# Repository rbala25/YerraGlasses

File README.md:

# YerraGlasses
 
Audio-augmented smart glasses that act as a wearable guide dog — real-time object detection converted to spatial audio feedback, all running on an ESP32-S3 tucked inside a glasses frame.
 
---
 
## Highlights
 
**Embedded ML Object Detection** — Neural network running on a **Luckfox RV1103 NPU** detects objects from live visual input and converts them into real-time auditory cues. Designed to assist blind and visually impaired users without any cloud dependency.
 
**Dual I2S Class-D Audio** — Two Class-D amplifiers driven over I2S deliver low-latency directional audio feedback. Custom DAC and speaker amplification stages built discrete, with 26-gauge wire crimped and routed by hand to fit the form factor.
 
**Space-Constrained PCB** — Custom board designed to fit inside a glasses frame. Integrates USB-C input, rail regulation, I2C sensor communication, and the full I2S audio pipeline — all in a footprint small enough to wear.
 
**Power System** — Robust battery management with USB-C charging, regulated power rails, and firmware-level power state detection to maximize battery life in a miniature form factor.
 
---
 
## Stack
 
| Layer | Tech |
|---|---|
| MCU | ESP32-S3 |
| Language | C, bare-metal |
| ML Inference | Luckfox RV1103 NPU (object detection) |
| Audio | Dual I2S Class-D amps + custom DAC |
| Communication | I2C |
| Power | USB-C + regulated rails + battery monitoring |
| Hardware | Custom PCB, 26-gauge hand-crimped wiring |

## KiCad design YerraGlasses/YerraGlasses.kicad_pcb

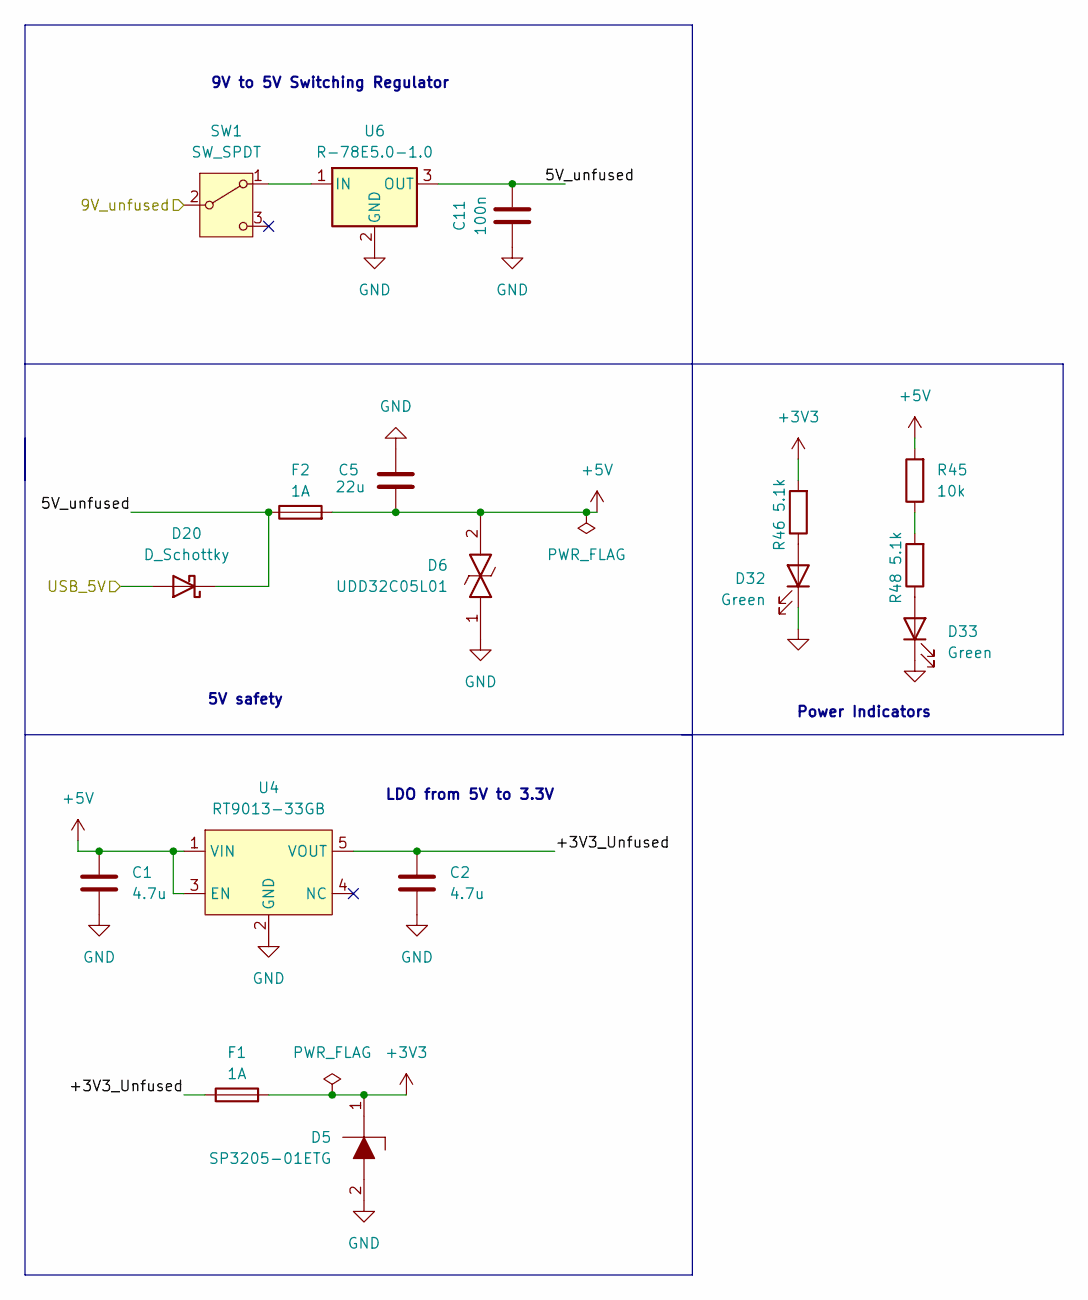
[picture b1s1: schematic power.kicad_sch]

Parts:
C1, C2: 4.7u; C_1206_3216Metric_Pad1.33x1.80mm_HandSolder; Mouser # 187-CL31A475KBHNNNE
C5: 22u; C_0603_1608Metric_Pad1.08x0.95mm_HandSolder; Mouser # 963-A168BB5226MTNA01
C11: 100n; C_0603_1608Metric_Pad1.08x0.95mm_HandSolder; Mouser # 581-KAM15BR72A104KT
D5: SP3205-01ETG; SP320501ETG; Mouser # 576-SP3205-01ETG
D6: UDD32C05L01; D_SOD-323; Mouser # 603-UDD32C05L01
D20: D_Schottky; D_PowerDI-123; Mouser # 621-DFLS160-F
D32, D33: Green; D_0603_1608Metric_Pad1.05x0.95mm_HandSolder; Mouser # 604-APT1608LZGCK
F1, F2: 1A; Fuse_0603_1608Metric_Pad1.05x0.95mm_HandSolder; Mouser # 504-TR-0603HV1-R
R45: 10k; R_0603_1608Metric_Pad0.98x0.95mm_HandSolder; Mouser # 71-CRCW0603-10K-E3
R46, R48: 5.1k; R_0603_1608Metric_Pad0.98x0.95mm_HandSolder; Mouser # 71-CRCW0603-5.1K-E3
SW1: SW_SPDT; SW_SPDT_PCM12; Mouser # 611-PCM12SMTBR
U4: RT9013-33GB; SOT-23-5; Mouser # 835-RT9013-33GB
U6: R-78E5.0-1.0; Converter_DCDC_RECOM_R-78E-0.5_THT; Mouser # 919-R-78E5.0-1.0; JLCPCB # C22371890

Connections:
+3V3: D5.1, F1.2, R46.2; also elsewhere on the board
+5V: C1.1, C5.1, D6.2, F2.2, R45.2, U4.1 (VIN), U4.3 (EN); also elsewhere on the board
/Connectors/9V_unfused: SW1.2 (B); also elsewhere on the board
/MCU/USB_5V: D20.2 (A); also elsewhere on the board
/Power/5V_unfused: C11.2, D20.1 (K), F2.1, U6.3 (OUT)
/Power/+3V3_Unfused: C2.1, F1.1, U4.5 (VOUT)
GND: C1.2, C2.2, C5.2, C11.1, D5.2, D6.1, D32.1 (K), D33.1 (K), U4.2 (GND), U6.2 (GND); also elsewhere on the board
unnamed: D32.2 (A), R46.1
unnamed: D33.2 (A), R48.1
unnamed: R45.1, R48.2
unnamed: SW1.1 (A), U6.1 (IN)

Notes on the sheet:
Power Indicators
LDO from 5V to 3.3V
5V safety
9V to 5V Switching Regulator

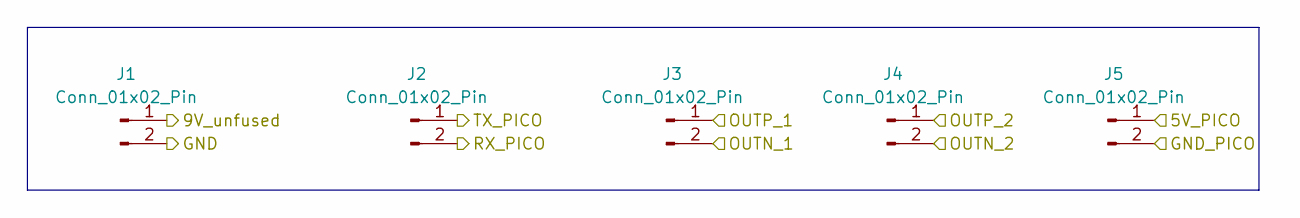
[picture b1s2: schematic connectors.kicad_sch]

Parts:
J1, J2, J3, J4, J5: Conn_01x02_Pin; JST_PH_B2B-PH-K_1x02_P2.00mm_Vertical; Mouser # 306-B2BPHKSLFSNPP; JLCPCB # C131337

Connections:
+5V: J5.1; also elsewhere on the board
/Connectors/9V_unfused: J1.1; also elsewhere on the board
/Connectors/OUTN_1: J3.2; also elsewhere on the board
/Connectors/OUTN_2: J4.2; also elsewhere on the board
/Connectors/OUTP_1: J3.1; also elsewhere on the board
/Connectors/OUTP_2: J4.1; also elsewhere on the board
/Connectors/RX_PICO: J2.2; also elsewhere on the board
/Connectors/TX_PICO: J2.1; also elsewhere on the board
GND: J1.2, J5.2; also elsewhere on the board

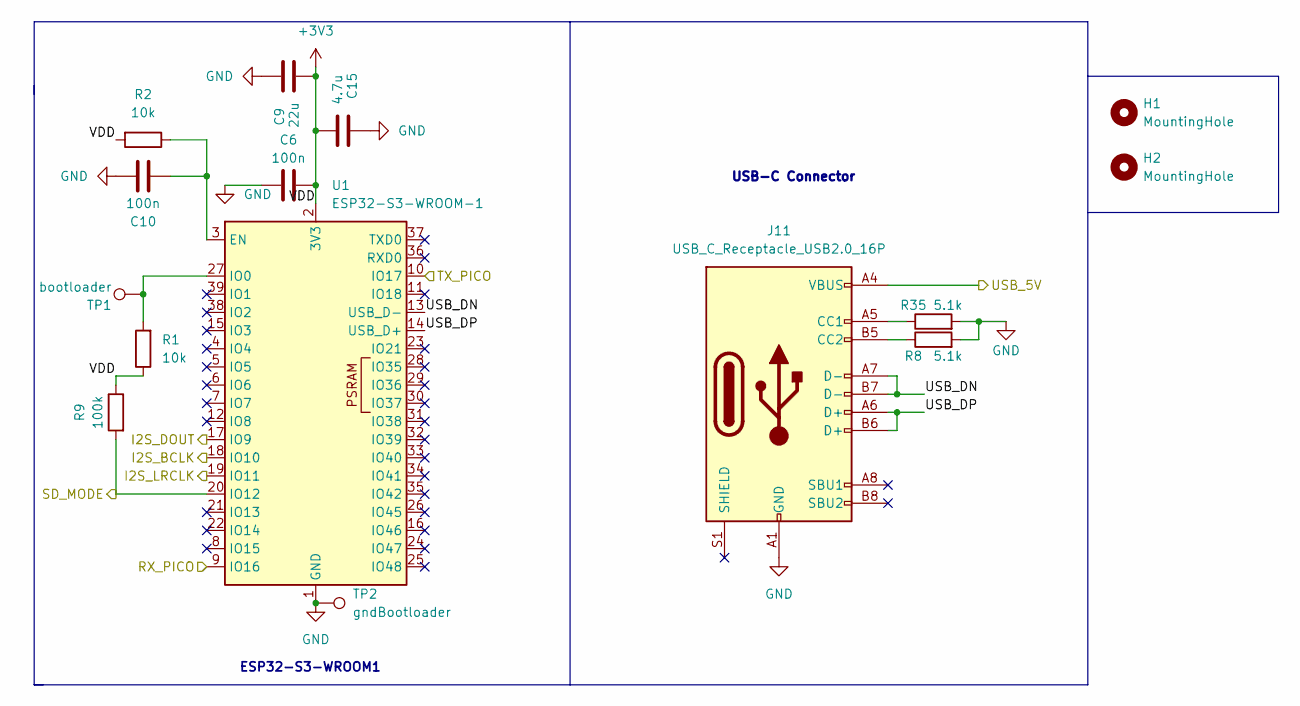
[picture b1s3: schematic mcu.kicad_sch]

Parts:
C6, C10: 100n; C_0603_1608Metric_Pad1.08x0.95mm_HandSolder; Mouser # 581-KAM15BR72A104KT
C9: 22u; C_0603_1608Metric_Pad1.08x0.95mm_HandSolder; Mouser # 963-A168BB5226MTNA01
C15: 4.7u; C_1206_3216Metric_Pad1.33x1.80mm_HandSolder; Mouser # 187-CL31A475KBHNNNE
H1, H2: MountingHole; MountingHole_2.2mm_M2_custom
J11: USB_C_Receptacle_USB2.0_16P; USB-C_2.0_Receptacle; Mouser # 640-USB4105-GF-A
R1, R2: 10k; R_0603_1608Metric_Pad0.98x0.95mm_HandSolder; Mouser # 71-CRCW0603-10K-E3
R8, R35: 5.1k; R_0603_1608Metric_Pad0.98x0.95mm_HandSolder; Mouser # 71-CRCW0603-5.1K-E3
R9: 100k; R_0603_1608Metric_Pad0.98x0.95mm_HandSolder; Mouser # 603-RC0603FR-07100KL
TP1: bootloader; TestPoint_Pad_1.0x1.0mm
TP2: gndBootloader; TestPoint_Pad_1.0x1.0mm
U1: ESP32-S3-WROOM-1; Mouser # 356-ESP32S3WROOM1N16; JLCPCB # C2913199

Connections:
+3V3: C6.2, C9.1, C15.1, R1.1, R2.2, R9.1, U1.2 (3V3); also elsewhere on the board
/Connectors/RX_PICO: U1.9 (IO16); also elsewhere on the board
/Connectors/TX_PICO: U1.10 (IO17); also elsewhere on the board
/MCU/I2S_BCLK: U1.18 (IO10); also elsewhere on the board
/MCU/I2S_DOUT: U1.17 (IO9); also elsewhere on the board
/MCU/I2S_LRCLK: U1.19 (IO11); also elsewhere on the board
/MCU/SD_MODE: R9.2, U1.20 (IO12); also elsewhere on the board
/MCU/USB_5V: J11.A4 (VBUS), J11.A9 (VBUS), J11.B4 (VBUS), J11.B9 (VBUS); also elsewhere on the board
/MCU/USB_DN: J11.A7 (D-), J11.B7 (D-), U1.13 (USB_D-)
/MCU/USB_DP: J11.A6 (D+), J11.B6 (D+), U1.14 (USB_D+)
GND: C6.1, C9.2, C10.2, C15.2, J11.A1 (GND), J11.A12 (GND), J11.B1 (GND), J11.B12 (GND), R8.2, R35.2, TP2.1, U1.1 (GND), U1.40 (GND), U1.41 (GND); also elsewhere on the board
unnamed: J11.A5 (CC1), R35.1
unnamed: J11.B5 (CC2), R8.1
unnamed: C10.1, R2.1, U1.3 (EN)
unnamed: R1.2, TP1.1, U1.27 (IO0)

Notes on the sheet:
ESP32-S3-WROOM1
USB-C Connector

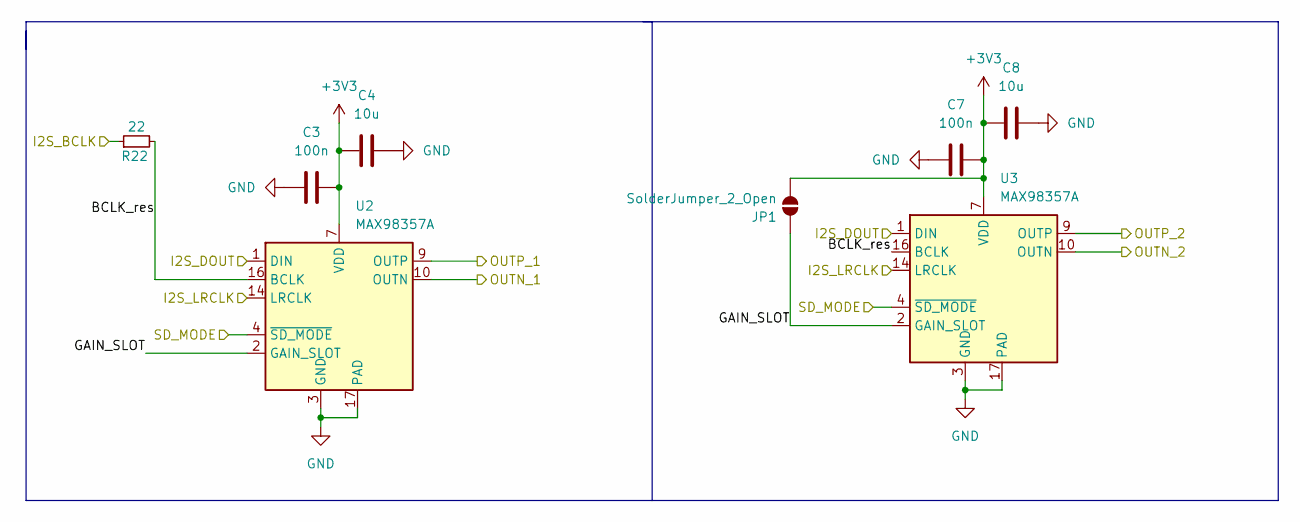
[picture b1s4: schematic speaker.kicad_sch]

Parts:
C3, C7: 100n; C_0603_1608Metric_Pad1.08x0.95mm_HandSolder; Mouser # 581-KAM15BR72A104KT
C4, C8: 10u; C_0805_2012Metric_Pad1.18x1.45mm_HandSolder; Mouser # 81-GRM21BR61H106KE3L
JP1: SolderJumper_2_Open; SolderJumper-2_P1.3mm_Open_RoundedPad1.0x1.5mm
R22: 22; R_0603_1608Metric_Pad0.98x0.95mm_HandSolder; Mouser # 71-CRCW0603-22-E3
U2, U3: MAX98357A; TQFN-16-1EP_3x3mm_P0.5mm_EP1.23x1.23mm; Mouser # 700-MAX98357AETE+T; JLCPCB # C910544

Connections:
+3V3: C3.2, C4.2, C7.2, C8.2, JP1.1 (A), U2.7 (VDD), U2.8 (VDD), U3.7 (VDD), U3.8 (VDD); also elsewhere on the board
/Connectors/OUTN_1: U2.10 (OUTN); also elsewhere on the board
/Connectors/OUTN_2: U3.10 (OUTN); also elsewhere on the board
/Connectors/OUTP_1: U2.9 (OUTP); also elsewhere on the board
/Connectors/OUTP_2: U3.9 (OUTP); also elsewhere on the board
/MCU/I2S_BCLK: R22.1; also elsewhere on the board
/MCU/I2S_DOUT: U2.1 (DIN), U3.1 (DIN); also elsewhere on the board
/MCU/I2S_LRCLK: U2.14 (LRCLK), U3.14 (LRCLK); also elsewhere on the board
/MCU/SD_MODE: U2.4 (~SD_MODE), U3.4 (~SD_MODE); also elsewhere on the board
/Speaker/BCLK_res: R22.2, U2.16 (BCLK), U3.16 (BCLK)
/Speaker/GAIN_SLOT: JP1.2 (B), U2.2 (GAIN_SLOT), U3.2 (GAIN_SLOT)
GND: C3.1, C4.1, C7.1, C8.1, U2.3 (GND), U2.11 (GND), U2.15 (GND), U2.17 (PAD), U3.3 (GND), U3.11 (GND), U3.15 (GND), U3.17 (PAD); also elsewhere on the board

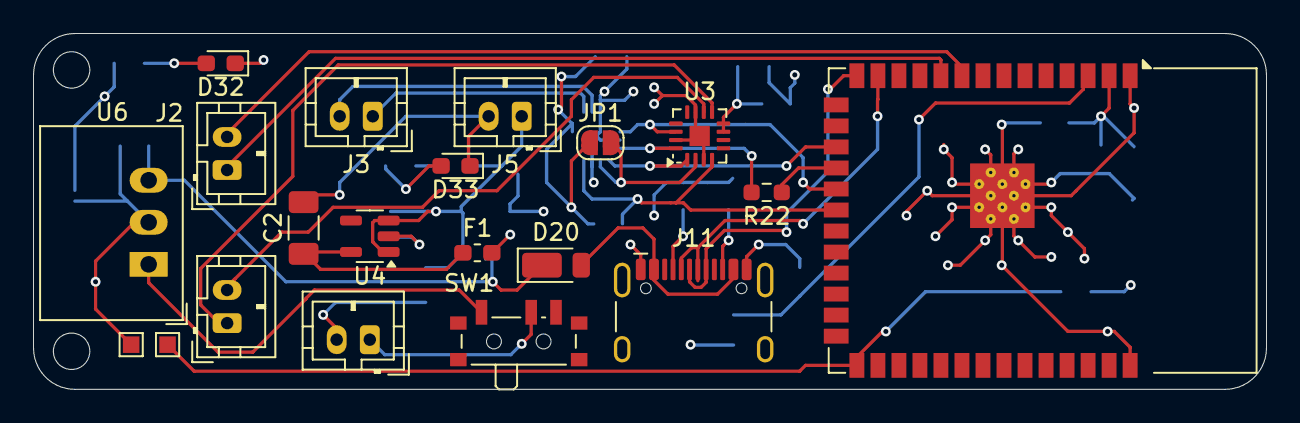
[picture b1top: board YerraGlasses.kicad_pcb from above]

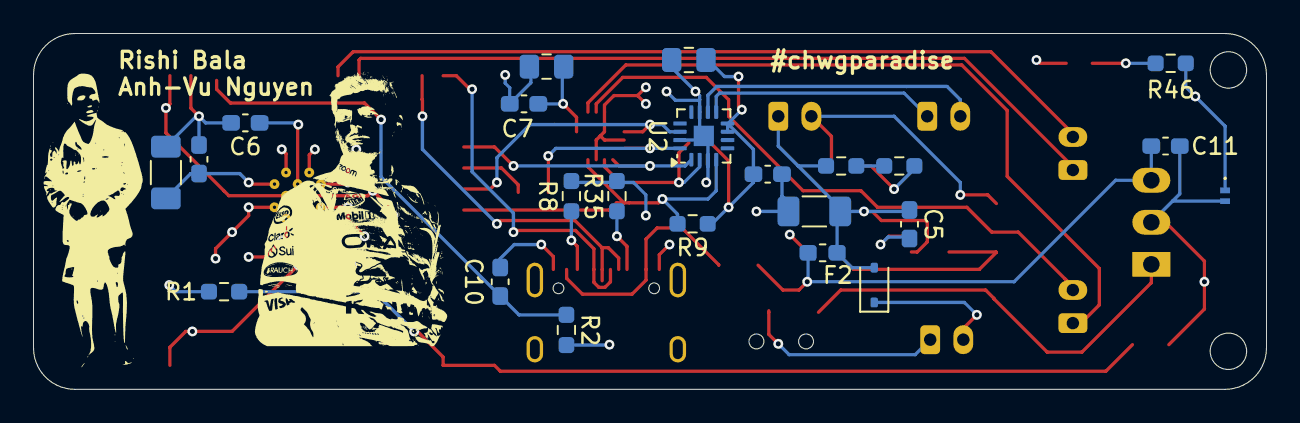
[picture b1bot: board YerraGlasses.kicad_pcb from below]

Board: 4 copper layers, 74.5 x 21.5 mm, 45 parts (23 on the bottom side), 29 nets.

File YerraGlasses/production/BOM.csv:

"Reference","Qty","Value","DNP","Exclude from BOM","Exclude from Board","Footprint","JLCPCB #","Mouser #","Mouser Link","Mouser Part Number"
"C1,C2,C15","3","4.7u","","","","Capacitor_SMD:C_1206_3216Metric_Pad1.33x1.80mm_HandSolder","C513768","187-CL31A475KBHNNNE","https://www.mouser.com/ProductDetail/Samsung-Electro-Mechani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","187-CL31A475KBHNNNE"
"C3,C6,C7,C10,C11","5","100n","","","","Capacitor_SMD:C_0603_1608Metric_Pad1.08x0.95mm_HandSolder","C14663","581-KAM15BR72A104KT","https://www.mouser.com/ProductDetail/KYOCERA-AVX/KAM15BR72A1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","581-KAM15BR72A104KT"
"C4,C8","2","10u","","","","Capacitor_SMD:C_0805_2012Metric_Pad1.18x1.45mm_HandSolder","C440198","81-GRM21BR61H106KE3L","https://www.mouser.com/ProductDetail/Murata-Electronics/GRM2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","81-GRM21BR61H106KE3L"
"C5,C9","2","22u","","","","Capacitor_SMD:C_0603_1608Metric_Pad1.08x0.95mm_HandSolder","C59461","963-A168BB5226MTNA01","https://www.mouser.com/ProductDetail/TAIYO-YUDEN/MSASA168BB5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","963-A168BB5226MTNA01"
"D5","1","SP3205-01ETG","","","","0_LHRE_Footprints:SP320501ETG","C19829542","576-SP3205-01ETG","https://www.mouser.com/ProductDetail/Littelfuse/SP3205-01ETG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","576-SP3205-01ETG"
"D6","1","UDD32C05L01","","","","Diode_SMD:D_SOD-323","C78440 ","603-UDD32C05L01","https://www.mouser.com/ProductDetail/YAGEO/UDD32C05L01?qs=0l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","603-UDD32C05L01"
"D20","1","D_Schottky","","","","Diode_SMD:D_PowerDI-123","C177023","621-DFLS160-F","https://www.mouser.com/ProductDetail/Diodes-Incorporated/DFL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","726-BAT60AE6327"
"D32,D33","2","Green","","","","Diode_SMD:D_0603_1608Metric_Pad1.05x0.95mm_HandSolder","C5246833","604-APT1608LZGCK","https://www.mouser.com/ProductDetail/Kingbright/APT1608LZGCK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","604-APT1608LZGCK"
"F1,F2","2","1A","","","","Fuse:Fuse_0603_1608Metric_Pad1.05x0.95mm_HandSolder","C136329","504-TR-0603HV1-R","https://www.mouser.com/ProductDetail/Eaton-Electronics/TR-06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","504-TR-0603HV1-R"
"H1,H2","2","MountingHole","","Excluded from BOM","","MountingHole:MountingHole_2.2mm_M2_custom","","","",""
"J1,J2,J3,J4,J5","5","Conn_01x02_Pin","","","","Connector_JST:JST_PH_B2B-PH-K_1x02_P2.00mm_Vertical","C131337","306-B2BPHKSLFSNPP","https://www.mouser.com/ProductDetail/JST-Commercial/B2B-PH-K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","306-B2BPHKSLFSNPP"
"J11","1","USB_C_Receptacle_USB2.0_16P","","","","0_LHRE_Footprints:USB-C_2.0_Receptacle","C2982555","640-USB4105-GF-A","https://www.mouser.com/ProductDetail/GCT/USB4105-GF-A?qs=KUo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","640-USB4105-GF-A"
"JP1","1","SolderJumper_2_Open","","Excluded from BOM","","Jumper:SolderJumper-2_P1.3mm_Open_RoundedPad1.0x1.5mm","","","",""
"R1,R2,R45","3","10k","","","","Resistor_SMD:R_0603_1608Metric_Pad0.98x0.95mm_HandSolder","C25804","71-CRCW0603-10K-E3","https://www.mouser.com/ProductDetail/Vishay/CRCW060310K0FKEA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","71-CRCW0603-10K-E3"
"R8,R35,R46,R48","4","5.1k","","","","Resistor_SMD:R_0603_1608Metric_Pad0.98x0.95mm_HandSolder","C23186","71-CRCW0603-5.1K-E3","https://www.mouser.com/ProductDetail/Vishay-Dale/CRCW06035K1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","71-CRCW0603-5.1K-E3"
"R9","1","100k","","","","Resistor_SMD:R_0603_1608Metric_Pad0.98x0.95mm_HandSolder","C14675","603-RC0603FR-07100KL","https://www.mouser.com/ProductDetail/YAGEO/RC0603FR-07100KL?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","603-RC0603FR-07100KL"
"R22","1","22","","","","Resistor_SMD:R_0603_1608Metric_Pad0.98x0.95mm_HandSolder","C23345","71-CRCW0603-22-E3 ","https://www.mouser.com/ProductDetail/Vishay-Dale/CRCW060322R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","71-CRCW0603-22-E3"
"SW1","1","SW_SPDT","","","","Button_Switch_SMD:SW_SPDT_PCM12","C319020","611-PCM12SMTBR","https://www.mouser.com/ProductDetail/CK/PCM12SMTBR?qs=By6Nw2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","611-PCM12SMTBR"
"TP1","1","bootloader","","Excluded from BOM","","TestPoint:TestPoint_Pad_1.0x1.0mm","","","",""
"TP2","1","gndBootloader","","Excluded from BOM","","TestPoint:TestPoint_Pad_1.0x1.0mm","","","",""
"U1","1","ESP32-S3-WROOM-1","","","","RF_Module:ESP32-S3-WROOM-1","C2913199","356-ESP32S3WROOM1N16","https://www.mouser.com/ProductDetail/Espressif-Systems/ESP32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","356-ESP32S3WROOM1N16"
"U2,U3","2","MAX98357A","","","","Package_DFN_QFN:TQFN-16-1EP_3x3mm_P0.5mm_EP1.23x1.23mm","C910544","700-MAX98357AETE+T","https://www.mouser.com/ProductDetail/Analog-Devices-Maxim-In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","700-MAX98357AETE+T"
"U4","1","RT9013-33GB","","","","Package_TO_SOT_SMD:SOT-23-5","C47773","835-RT9013-33GB","https://www.mouser.com/ProductDetail/Richtek/RT9013-33GB?qs=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","835-RT9013-33GB"
"U6","1","R-78E5.0-1.0","","","","Converter_DCDC:Converter_DCDC_RECOM_R-78E-0.5_THT","C22371890","919-R-78E5.0-1.0","https://www.mouser.com/ProductDetail/RECOM-Power/R-78E5.0-1.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","919-R-78E5.0-1.0"

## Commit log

2026-01-15 init PCB
2026-01-16 schematic
2026-01-16 init layout
2026-01-16 horizontal layout ver
2026-01-16 horiz layout changes
2026-01-16 pcb mounting, silkscreen, started CAD
2026-01-16 pcb finalized, started cad files, silkscreen
2026-01-16 added power connector, updated cad
2026-01-16 production for jlc
2026-01-16 clean up
2026-01-17 updated cad
2026-01-18 cad completion prototype
2026-01-18 updated cad, code start
2026-01-18 updated pcb cad
2026-01-21 printable cad
2026-01-23 cad, pcb updaates
2026-01-25 updated pcb order, cad
2026-01-28 jlc order
2026-01-30 esp32-s3 code init
2026-01-30 updated for pin outs
2026-02-16 spiffs and updated
2026-02-16 built
2026-02-28 first flashgit add .git add .git add .git add .
2026-02-28 uart to i2c
2026-03-28 i2c to uart
2026-03-28 remove .history from tracking
2026-03-28 updated format string
2026-03-28 software cofirmed
2026-04-21 Revise README to include project details and tech stack
    Added detailed project description, highlights, and technology stack for YerraGlasses.
